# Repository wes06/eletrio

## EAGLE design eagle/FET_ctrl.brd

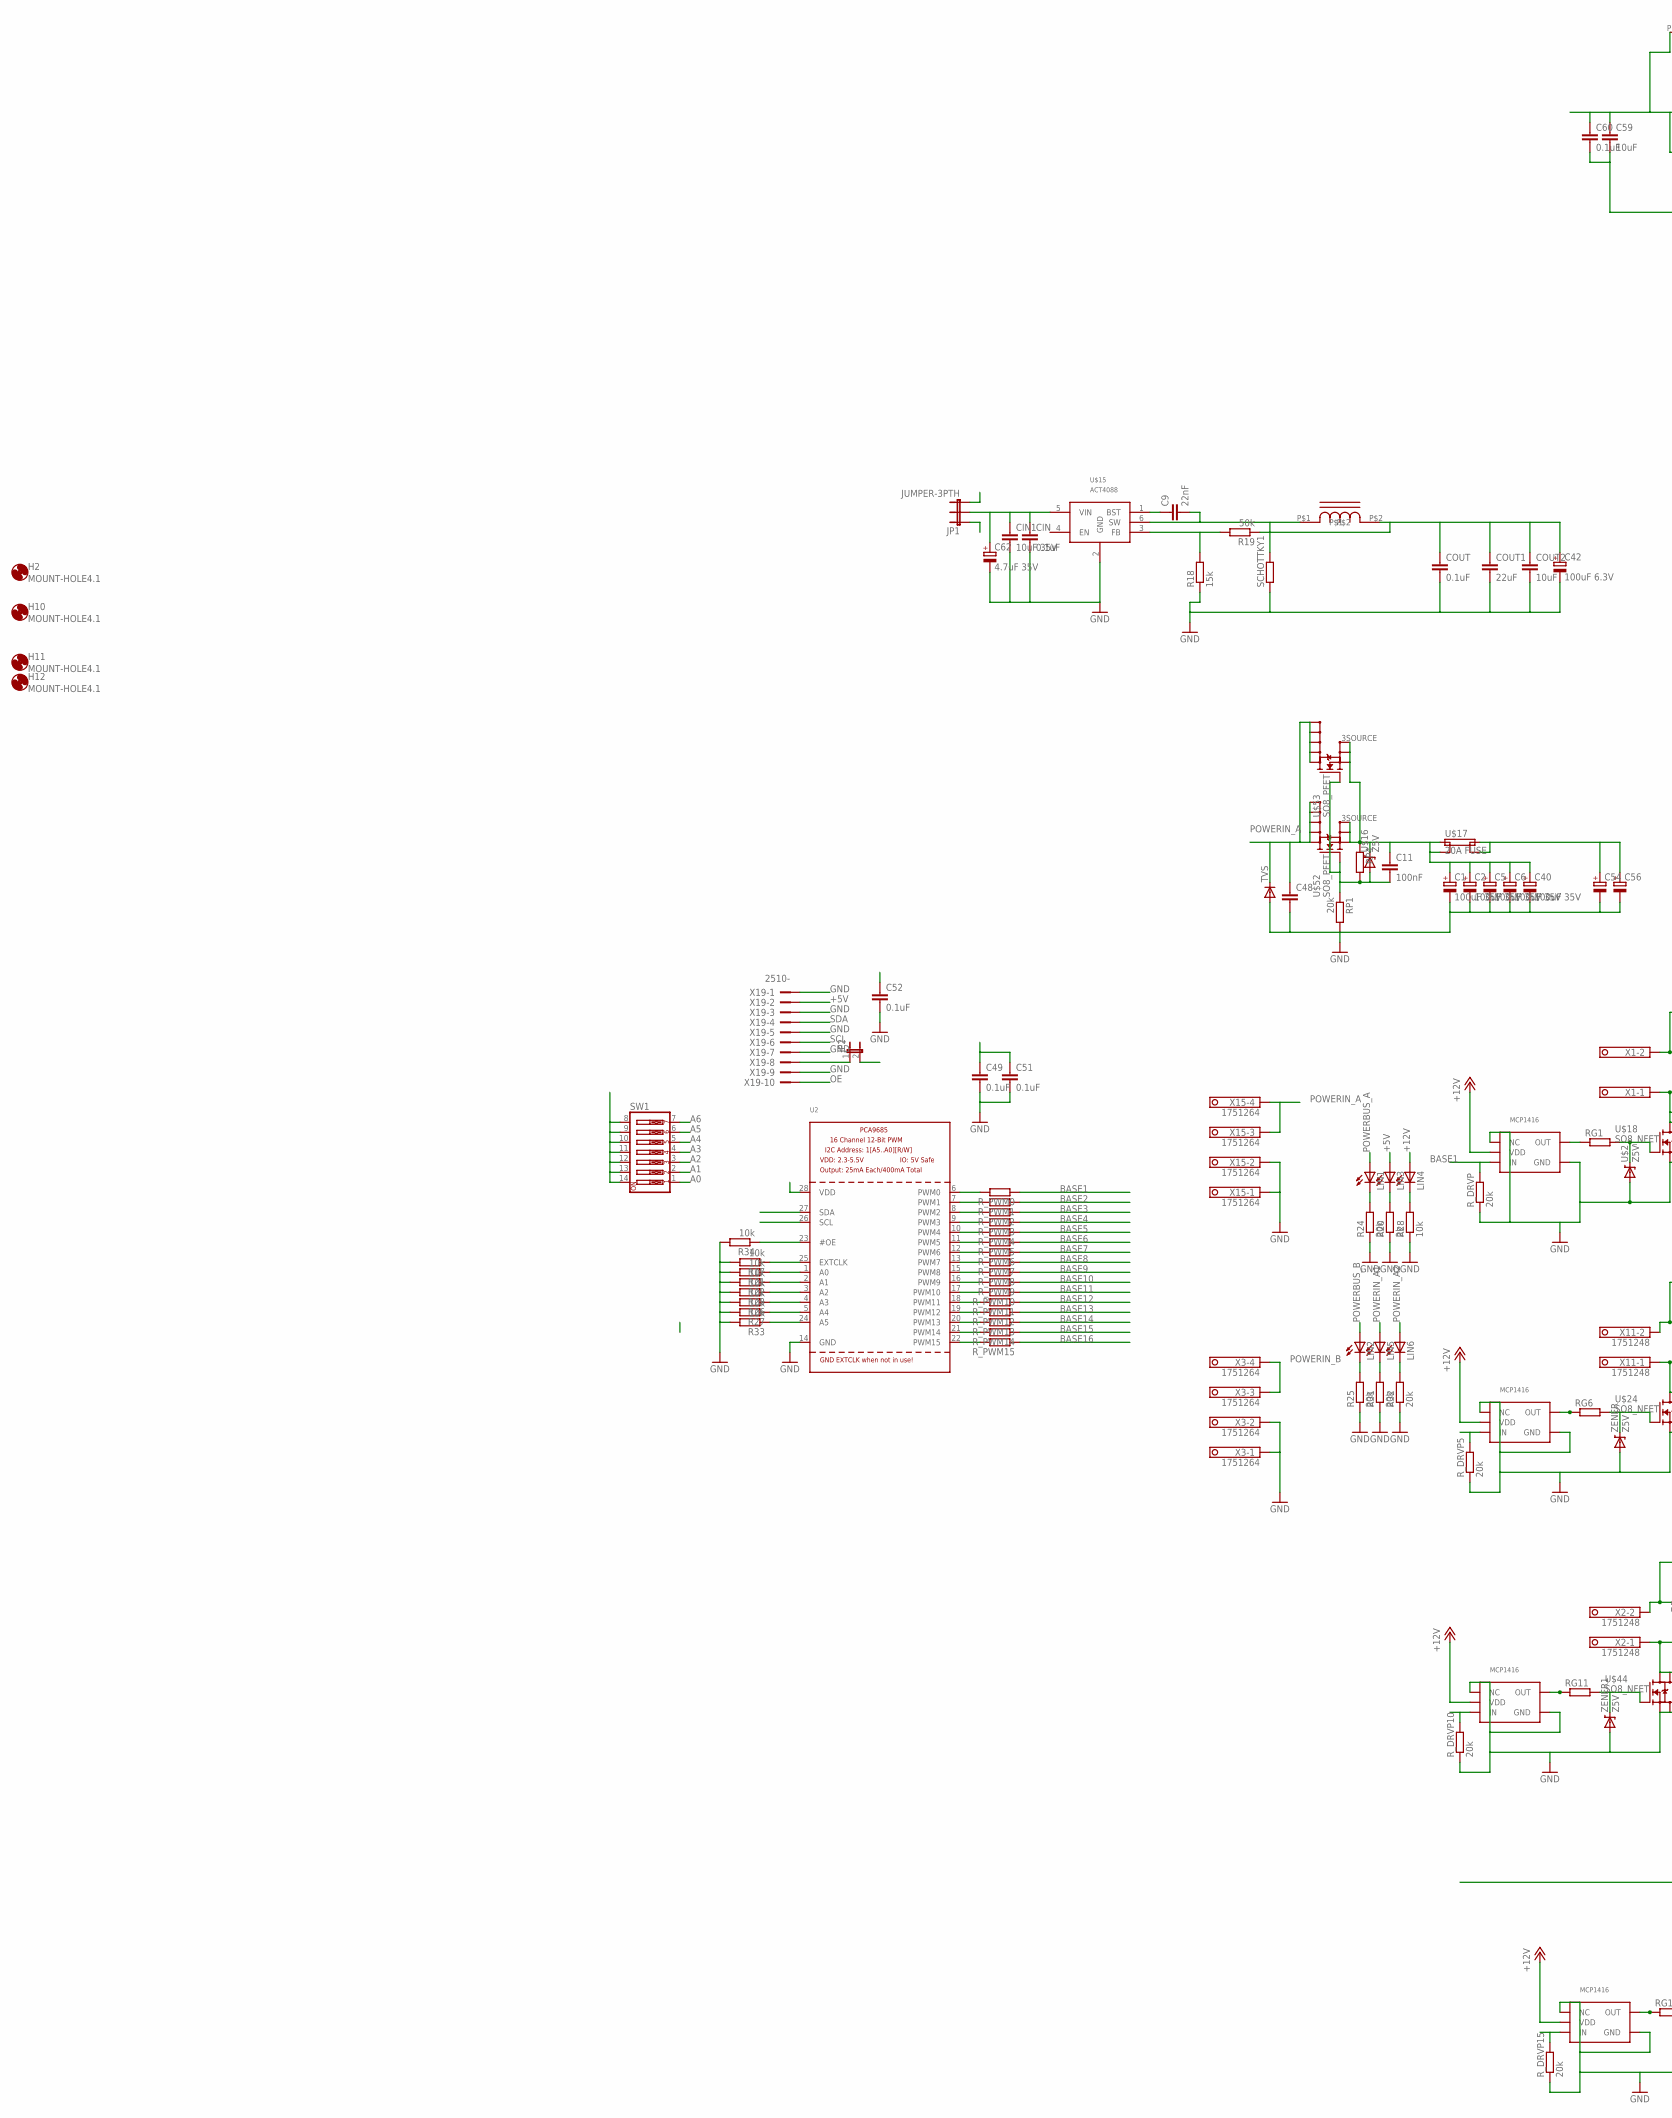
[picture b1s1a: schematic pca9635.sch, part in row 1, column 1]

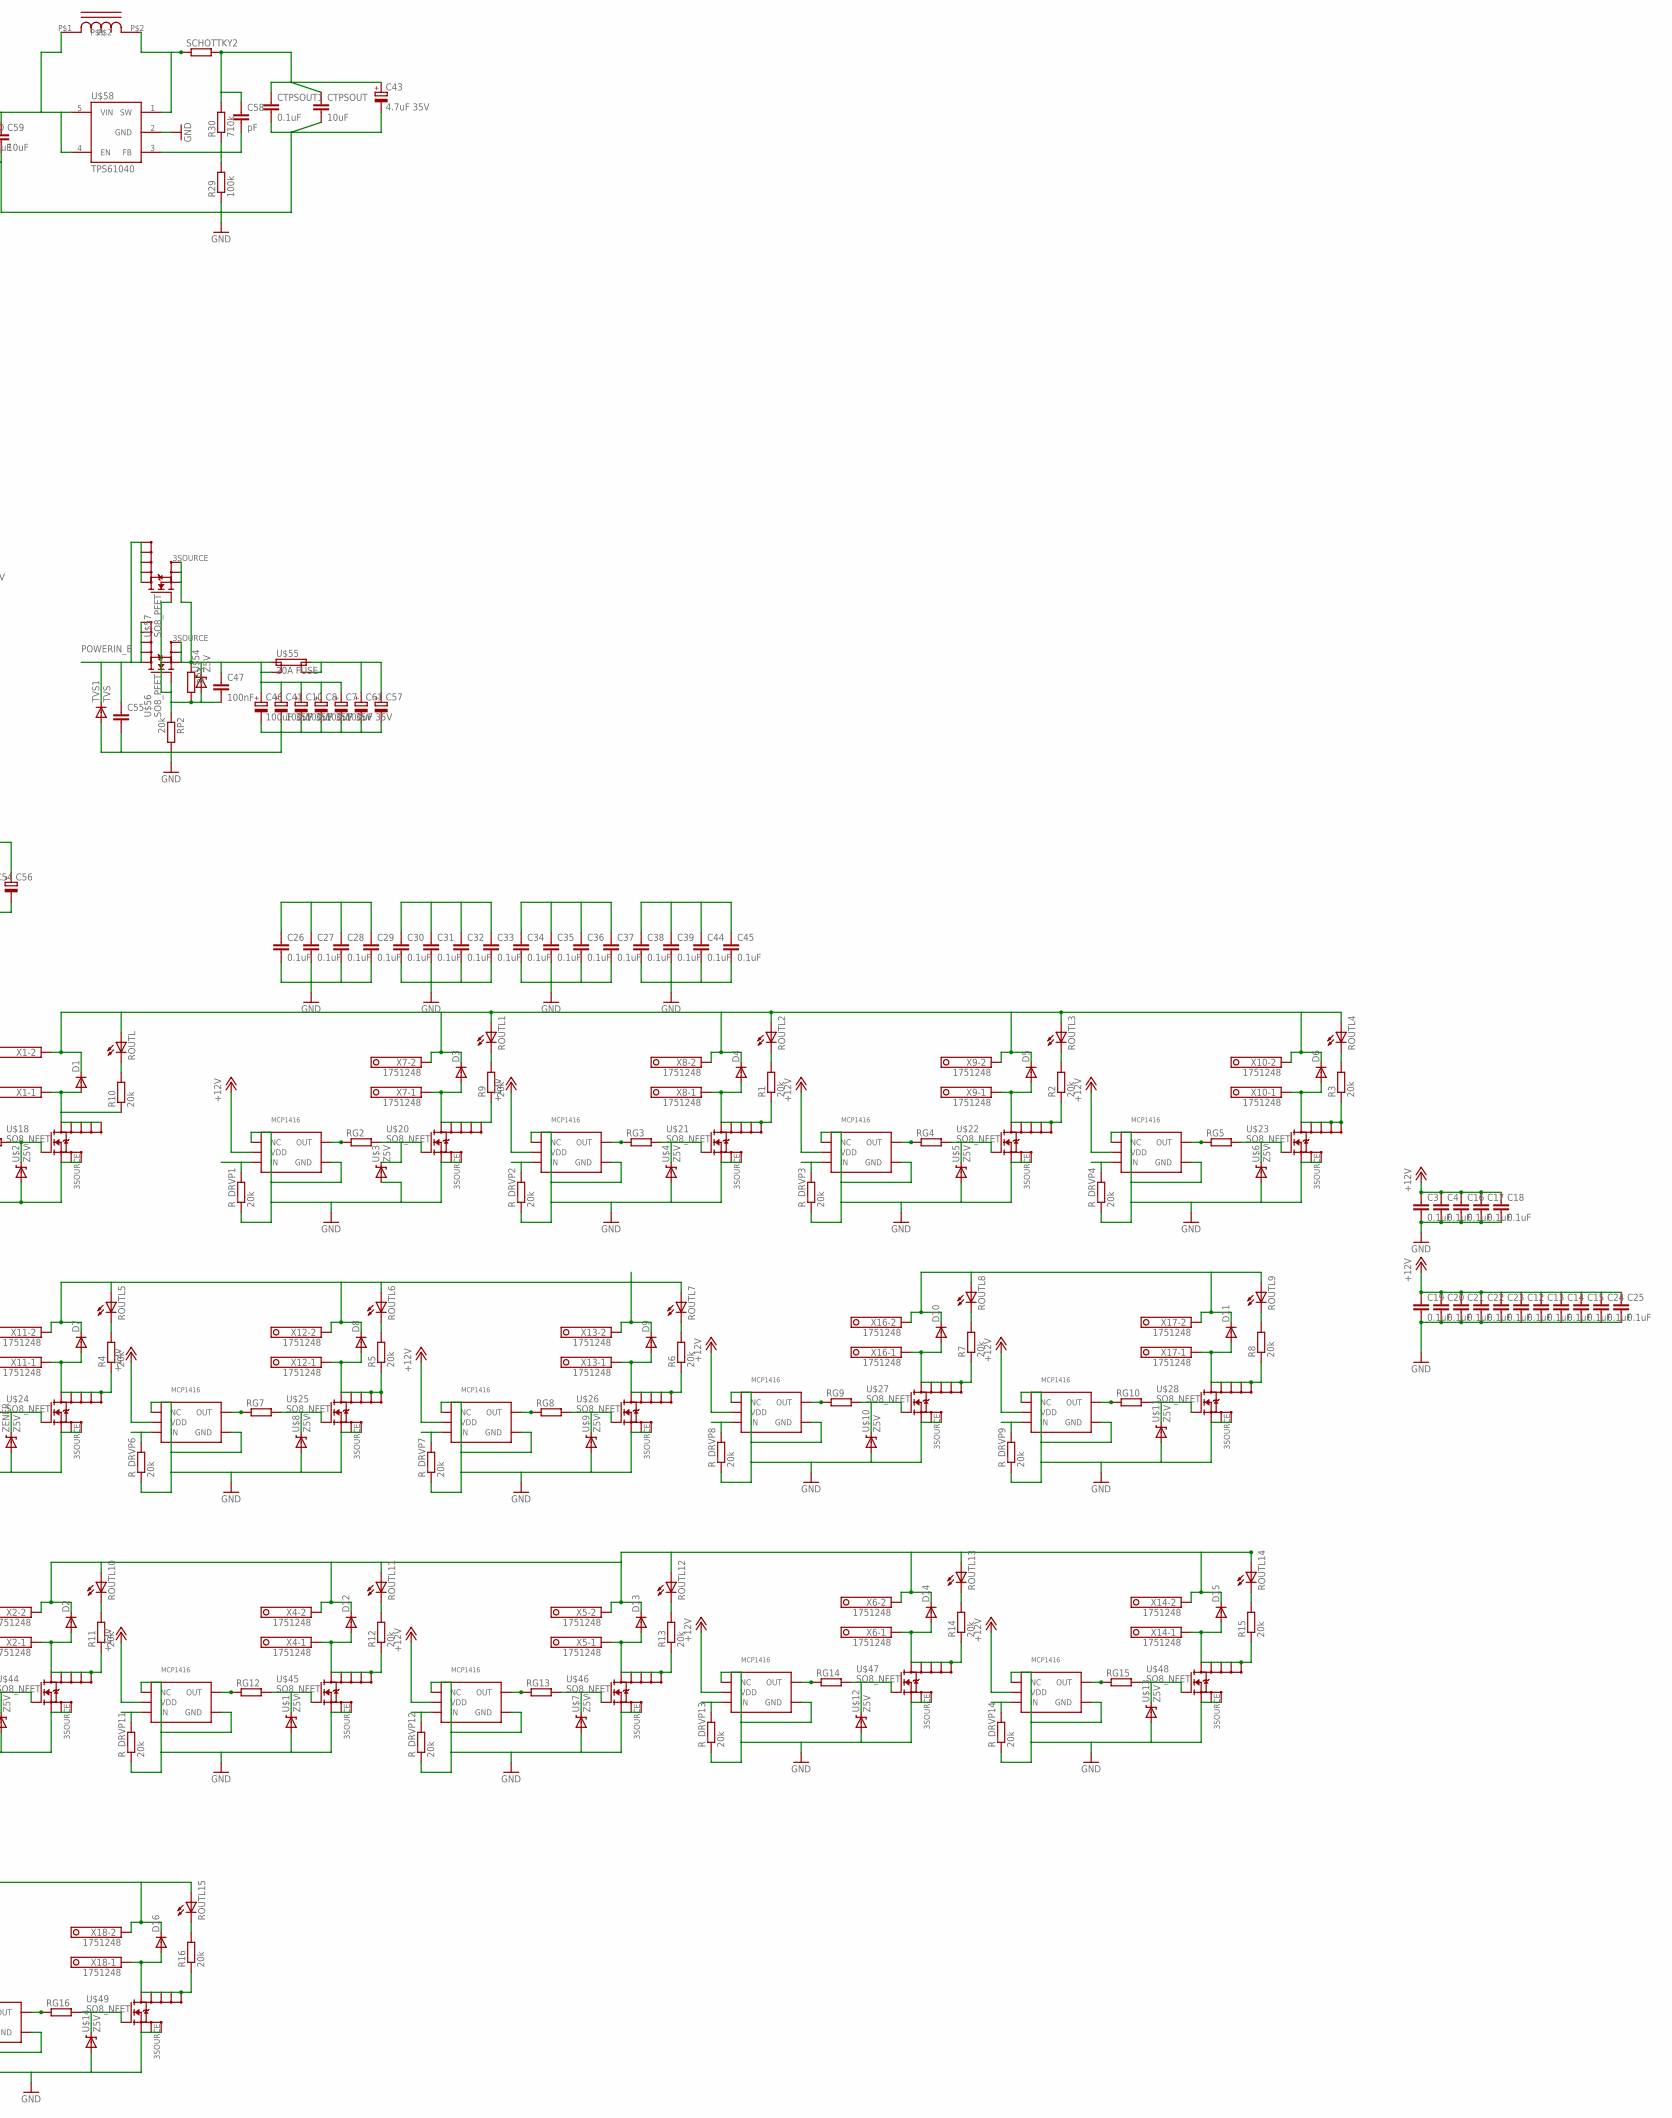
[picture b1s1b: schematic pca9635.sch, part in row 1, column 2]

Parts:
C1, C2, C5, C6, C7, C8, C10, C40, C41, C46: 100uF 35V; SMD_8X10_3.5HOLE
C3, C4, C12, C13, C14, C15, C16, C17, C18, C19, C20, C21, C22, C23, C24, C25, C26, C27, C28, C29, C30, C31, C32, C33, C34, C35, C36, C37, C38, C39, C44, C45, C49, C51, C52, C60: 0.1uF; C0603
C9: 22nF; C0805
C11, C47: 100nF; C0603
C42: 100uF 6.3V; UD-4X5,8_NICHICON
C43, C62: 4.7uF 35V; UD-4X5,8_NICHICON
C48, C55: C-EU050-055X075; C050-055X075
C54, C56, C57, C61: CPOL-EUUD-6,3X7,7; UD-6,3X7,7_NICHICON
C58: pF; C0603
C59: 10uF; C1206
CIN: 0.1uF; C0805
CIN1: 10uF 35V; C1206
COUT: 0.1uF; C0603
COUT1: 22uF; C1210
COUT2: 10uF; C1206
CTPSOUT: 10uF; C1206
CTPSOUT1: 0.1uF; C0805
D1, D2, D3, D4, D5, D6, D7, D8, D9, D10, D11, D12, D13, D14, D15, D16: DIODESMA-ALT; SMA-DIODE_ALT
H2, H10, H11, H12: MOUNT-HOLE4.1; 4,1
JP1: JUMPER-3PTH; 1X03
JP2: JUMPER-2SMD-NO; SJ_2S-NO
LIN1, LIN2, LIN3, LIN4, LIN5, LIN6: LEDCHIP-LED0805; CHIP-LED0805
R1, R2, R3, R4, R5, R6, R7, R8, R9, R10, R11, R12, R13, R14, R15, R16, R24, R25, R31, R32: 20k; R0603
R17, R21, R22, R23, R26, R27, R28, R33, R34: 10k; R0603
R18: 15k; R0603
R19: 50k; R0603
R20: 2k; R0603
R29: 100k; R0603
R30: 710k; R0603
RG1, RG2, RG3, RG4, RG5, RG6, RG7, RG8, RG9, RG10, RG11, RG12, RG13, RG14, RG15, RG16: R-EU_R0603; R0603
ROUTL, ROUTL1, ROUTL2, ROUTL3, ROUTL4, ROUTL5, ROUTL6, ROUTL7, ROUTL8, ROUTL9, ROUTL10, ROUTL11, ROUTL12, ROUTL13, ROUTL14, ROUTL15: LEDCHIP-LED0805; CHIP-LED0805
RP1, RP2: 20k; R0603
RP3, RP4: R-EU_R0603; R0603
R_DRVP, R_DRVP1, R_DRVP2, R_DRVP3, R_DRVP4, R_DRVP5, R_DRVP6, R_DRVP7, R_DRVP8, R_DRVP9, R_DRVP10, R_DRVP11, R_DRVP12, R_DRVP13, R_DRVP14, R_DRVP15: 20k; R0603
R_PWM0, R_PWM1, R_PWM2, R_PWM3, R_PWM4, R_PWM5, R_PWM6, R_PWM7, R_PWM8, R_PWM9, R_PWM10, R_PWM11, R_PWM12, R_PWM13, R_PWM14, R_PWM15: R-EU_R0603; R0603
SCHOTTKY1, SCHOTTKY2: R-EU_R1206; R1206
SW1: SW_DIP-7; EDG-07
TVS: DIODE-SMC; SMC
TVS1: TVS; SMC
U2: PCA9685; TSSOP28
U$1, U$2, U$3, U$4, U$5, U$6, U$7, U$8, U$9, U$10, U$11, U$12, U$13, U$14, U$16, U$54: Z5V; SOD-323
U$15: ACT4088; SOT23-6
U$17, U$55: 20A FUSE; FUSE-3564-297-997
U$18, U$20, U$21, U$22, U$23, U$24, U$25, U$26, U$27, U$28, U$44, U$45, U$46, U$47, U$48, U$49: SO8_NFET; POWER-SO8
U$19, U$29, U$30, U$31, U$32, U$33, U$34, U$35, U$36, U$37, U$38, U$39, U$40, U$41, U$42, U$43: MCP1416; SOT23-5
U$52, U$53, U$56, U$57: SO8_PFET; POWER-SO8
U$58: TPS61040; SOT23-5
U$59, U$60: L1212; 1212
X1, X2, X4, X5, X6, X7, X8, X9, X10, X11, X12, X13, X14, X16, X17, X18: 1751248
X3, X15: 1751264
X19: 2510-; PAK100/2500-10
ZENER, ZENER1: Z5V; SOD-323

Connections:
+5V: C42.+, C49.1, C51.1, C52.1, C59.1, C60.1, COUT.1, COUT1.1, COUT2.1, LIN3.A, R19.1, SW1.8, SW1.9, SW1.10, SW1.11, SW1.12, SW1.13, SW1.14, U2.28 (VDD), U$58.4 (EN), U$58.5 (VIN), U$59.P$1, U$60.P$2, X19.2
+12V: C3.1, C4.1, C12.1, C13.1, C14.1, C15.1, C16.1, C17.1, C18.1, C19.1, C20.1, C21.1, C22.1, C23.1, C24.1, C25.1, C43.+, C58.1, CTPSOUT.1, CTPSOUT1.1, LIN4.A, R30.2, SCHOTTKY2.2, U$19.2 (VDD), U$29.2 (VDD), U$30.2 (VDD), U$31.2 (VDD), U$32.2 (VDD), U$33.2 (VDD), U$34.2 (VDD), U$35.2 (VDD), U$36.2 (VDD), U$37.2 (VDD), U$38.2 (VDD), U$39.2 (VDD), U$40.2 (VDD), U$41.2 (VDD), U$42.2 (VDD), U$43.2 (VDD)
A0: R21.1, SW1.1, U2.1 (A0)
A1: R22.1, SW1.2, U2.2 (A1)
A2: R23.1, SW1.3, U2.3 (A2)
A3: R26.1, SW1.4, U2.4 (A3)
A4: R27.1, SW1.5, U2.5 (A4)
A5: R33.1, SW1.6, U2.24 (A5)
A6: JP2.2, R17.1, SW1.7, U2.25 (EXTCLK)
BASE1: R_DRVP.2, R_PWM0.1, U$19.3 (IN)
BASE2: R_DRVP1.2, R_PWM1.1, U$29.3 (IN)
BASE3: R_DRVP2.2, R_PWM2.1, U$30.3 (IN)
BASE4: R_DRVP3.2, R_PWM3.1, U$31.3 (IN)
BASE5: R_DRVP4.2, R_PWM4.1, U$32.3 (IN)
BASE6: R_DRVP5.2, R_PWM5.1, U$33.3 (IN)
BASE7: R_DRVP6.2, R_PWM6.1, U$34.3 (IN)
BASE8: R_DRVP7.2, R_PWM7.1, U$35.3 (IN)
BASE9: R_DRVP8.2, R_PWM8.1, U$36.3 (IN)
BASE10: R_DRVP9.2, R_PWM9.1, U$37.3 (IN)
BASE11: R_DRVP10.2, R_PWM10.1, U$38.3 (IN)
BASE12: R_DRVP11.2, R_PWM11.1, U$39.3 (IN)
BASE13: R_DRVP12.2, R_PWM12.1, U$40.3 (IN)
BASE14: R_DRVP13.2, R_PWM13.1, U$41.3 (IN)
BASE15: R_DRVP14.2, R_PWM14.1, U$42.3 (IN)
BASE16: R_DRVP15.2, R_PWM15.1, U$43.3 (IN)
EXTCLK: JP2.1, X19.8
GND: C1.-, C1.-1 (-), C2.-, C2.-1 (-), C3.2, C4.2, C5.-, C5.-1 (-), C6.-, C6.-1 (-), C7.-, C7.-1 (-), C8.-, C8.-1 (-), C10.-, C10.-1 (-), C12.2, C13.2, C14.2, C15.2, C16.2, C17.2, C18.2, C19.2, C20.2, C21.2, C22.2, C23.2, C24.2, C25.2, C26.2, C27.2, C28.2, C29.2, C30.2, C31.2, C32.2, C33.2, C34.2, C35.2, C36.2, C37.2, C38.2, C39.2, C40.-, C40.-1 (-), C41.-, C41.-1 (-), C42.-, C43.-, C44.2, C45.2, C46.-, C46.-1 (-), C48.2, C49.2, C51.2, C52.2, C54.-, C55.2, C56.-, C57.-, C59.2, C60.2, C61.-, C62.-, CIN.2, CIN1.2, COUT.2, COUT1.2, COUT2.2, CTPSOUT.2, CTPSOUT1.2, R17.2, R18.1, R20.1, R21.2, R22.2, R23.2, R24.1, R25.1, R26.2, R27.2, R28.1, R29.1, R31.1, R32.1, R33.2, R34.2, RP1.2, RP2.2, R_DRVP.1, R_DRVP1.1, R_DRVP2.1, R_DRVP3.1, R_DRVP4.1, R_DRVP5.1, R_DRVP6.1, R_DRVP7.1, R_DRVP8.1, R_DRVP9.1, R_DRVP10.1, R_DRVP11.1, R_DRVP12.1, R_DRVP13.1, R_DRVP14.1, R_DRVP15.1, SCHOTTKY1.1, TVS.A, TVS1.A, U2.14 (GND), U$1.2 (A), U$2.2 (A), U$3.2 (A), U$4.2 (A), U$5.2 (A), U$6.2 (A), U$7.2 (A), U$8.2 (A), U$9.2 (A), U$10.2 (A), U$11.2 (A), U$12.2 (A), U$13.2 (A), U$14.2 (A), U$15.2 (GND), U$18.1SOURCE (S1), U$18.2SOURCE (S2), U$18.3SOURCE (S3), U$19.1 (NC), U$19.4 (GND), U$20.1SOURCE (S1), U$20.2SOURCE (S2), U$20.3SOURCE (S3), U$21.1SOURCE (S1), U$21.2SOURCE (S2), U$21.3SOURCE (S3), U$22.1SOURCE (S1), U$22.2SOURCE (S2), U$22.3SOURCE (S3), U$23.1SOURCE (S1), U$23.2SOURCE (S2), U$23.3SOURCE (S3), U$24.1SOURCE (S1), U$24.2SOURCE (S2), U$24.3SOURCE (S3), U$25.1SOURCE (S1), U$25.2SOURCE (S2), U$25.3SOURCE (S3), U$26.1SOURCE (S1), U$26.2SOURCE (S2), U$26.3SOURCE (S3), U$27.1SOURCE (S1), U$27.2SOURCE (S2), U$27.3SOURCE (S3), U$28.1SOURCE (S1), U$28.2SOURCE (S2), U$28.3SOURCE (S3), U$29.1 (NC), U$29.4 (GND), U$30.1 (NC), U$30.4 (GND), U$31.1 (NC), U$31.4 (GND), U$32.1 (NC), U$32.4 (GND), U$33.1 (NC), U$33.4 (GND), U$34.1 (NC), U$34.4 (GND), U$35.1 (NC), U$35.4 (GND), U$36.1 (NC), U$36.4 (GND), U$37.1 (NC), U$37.4 (GND), U$38.1 (NC), U$38.4 (GND), U$39.1 (NC), U$39.4 (GND), U$40.1 (NC), U$40.4 (GND), U$41.1 (NC), U$41.4 (GND), U$42.1 (NC), U$42.4 (GND), U$43.1 (NC), U$43.4 (GND), U$44.1SOURCE (S1), U$44.2SOURCE (S2), U$44.3SOURCE (S3), U$45.1SOURCE (S1), U$45.2SOURCE (S2), U$45.3SOURCE (S3), U$46.1SOURCE (S1), U$46.2SOURCE (S2), U$46.3SOURCE (S3), U$47.1SOURCE (S1), U$47.2SOURCE (S2), U$47.3SOURCE (S3), U$48.1SOURCE (S1), U$48.2SOURCE (S2), U$48.3SOURCE (S3), U$49.1SOURCE (S1), U$49.2SOURCE (S2), U$49.3SOURCE (S3), U$58.2 (GND), X3.1, X3.2, X15.1, X15.2, X19.1, X19.3, X19.5, X19.7, X19.9, ZENER.2 (A), ZENER1.2 (A)
unnamed: D1.A, R10.1, U$18.5DRAIN (D5), U$18.6DRAIN (D6), U$18.7DRAIN (D7), U$18.8DRAIN (D8), U$18.PAD_DRAIN (DPAD), X1.1
unnamed: R10.2, ROUTL.C
unnamed: D2.A, R11.1, U$44.5DRAIN (D5), U$44.6DRAIN (D6), U$44.7DRAIN (D7), U$44.8DRAIN (D8), U$44.PAD_DRAIN (DPAD), X2.1
unnamed: RG11.2, U$44.4GATE (G), ZENER1.1 (C)
unnamed: LIN3.C, R20.2
unnamed: D12.A, R12.1, U$45.5DRAIN (D5), U$45.6DRAIN (D6), U$45.7DRAIN (D7), U$45.8DRAIN (D8), U$45.PAD_DRAIN (DPAD), X4.1
unnamed: RG12.2, U$1.1 (C), U$45.4GATE (G)
unnamed: R1.2, ROUTL2.C
unnamed: D13.A, R13.1, U$46.5DRAIN (D5), U$46.6DRAIN (D6), U$46.7DRAIN (D7), U$46.8DRAIN (D8), U$46.PAD_DRAIN (DPAD), X5.1
unnamed: RG13.2, U$7.1 (C), U$46.4GATE (G)
unnamed: C47.2, RP2.1, RP3.2, U$54.2 (A), U$56.4GATE (G), U$57.4GATE (G)
unnamed: D14.A, R14.1, U$47.5DRAIN (D5), U$47.6DRAIN (D6), U$47.7DRAIN (D7), U$47.8DRAIN (D8), U$47.PAD_DRAIN (DPAD), X6.1
unnamed: RG14.2, U$12.1 (C), U$47.4GATE (G)
unnamed: R2.2, ROUTL3.C
unnamed: LIN2.C, R25.2
unnamed: D15.A, R15.1, U$48.5DRAIN (D5), U$48.6DRAIN (D6), U$48.7DRAIN (D7), U$48.8DRAIN (D8), U$48.PAD_DRAIN (DPAD), X14.1
unnamed: RG15.2, U$13.1 (C), U$48.4GATE (G)
unnamed: LIN4.C, R28.2
unnamed: R_PWM0.2, U2.6 (PWM0)
unnamed: R_PWM1.2, U2.7 (PWM1)
unnamed: R_PWM15.2, U2.22 (PWM15)
unnamed: R_PWM14.2, U2.21 (PWM14)
unnamed: R_PWM13.2, U2.20 (PWM13)
unnamed: D16.A, R16.1, U$49.5DRAIN (D5), U$49.6DRAIN (D6), U$49.7DRAIN (D7), U$49.8DRAIN (D8), U$49.PAD_DRAIN (DPAD), X18.1
unnamed: RG16.2, U$14.1 (C), U$49.4GATE (G)
unnamed: R3.2, ROUTL4.C
unnamed: R_PWM12.2, U2.19 (PWM12)
unnamed: R18.2, R19.2, U$15.3 (FB)
unnamed: C9.1, U$15.1 (BST)
unnamed: SCHOTTKY2.1, U$58.1 (SW), U$59.P$2
unnamed: LIN5.C, R31.2
unnamed: C58.2, R29.2, R30.1, U$58.3 (FB)
unnamed: LIN1.C, R24.2
unnamed: LIN6.C, R32.2
unnamed: C11.2, RP1.1, RP4.2, U$16.2 (A), U$52.4GATE (G), U$53.4GATE (G)
unnamed: RG1.1, U$19.5 (OUT)
unnamed: R_PWM11.2, U2.18 (PWM11)
unnamed: R_PWM10.2, U2.17 (PWM10)
unnamed: R_PWM9.2, U2.16 (PWM9)
unnamed: R_PWM8.2, U2.15 (PWM8)
unnamed: R_PWM7.2, U2.13 (PWM7)
unnamed: R_PWM6.2, U2.12 (PWM6)
unnamed: R_PWM5.2, U2.11 (PWM5)
unnamed: R_PWM4.2, U2.10 (PWM4)
unnamed: R_PWM3.2, U2.9 (PWM3)
unnamed: R_PWM2.2, U2.8 (PWM2)
unnamed: RG2.1, U$29.5 (OUT)
unnamed: RG3.1, U$30.5 (OUT)
unnamed: RG4.1, U$31.5 (OUT)
unnamed: D3.A, R9.1, U$20.5DRAIN (D5), U$20.6DRAIN (D6), U$20.7DRAIN (D7), U$20.8DRAIN (D8), U$20.PAD_DRAIN (DPAD), X7.1
unnamed: RG2.2, U$3.1 (C), U$20.4GATE (G)
unnamed: RG5.1, U$32.5 (OUT)
unnamed: RG6.1, U$33.5 (OUT)
unnamed: D4.A, R1.1, U$21.5DRAIN (D5), U$21.6DRAIN (D6), U$21.7DRAIN (D7), U$21.8DRAIN (D8), U$21.PAD_DRAIN (DPAD), X8.1
unnamed: RG7.1, U$34.5 (OUT)
unnamed: RG8.1, U$35.5 (OUT)
unnamed: RG3.2, U$4.1 (C), U$21.4GATE (G)
unnamed: R4.2, ROUTL5.C
unnamed: RG9.1, U$36.5 (OUT)
unnamed: RG10.1, U$37.5 (OUT)
unnamed: RG1.2, U$2.1 (C), U$18.4GATE (G)
unnamed: RG4.2, U$5.1 (C), U$22.4GATE (G)
unnamed: RG11.1, U$38.5 (OUT)
unnamed: RG12.1, U$39.5 (OUT)
unnamed: D6.A, R3.1, U$23.5DRAIN (D5), U$23.6DRAIN (D6), U$23.7DRAIN (D7), U$23.8DRAIN (D8), U$23.PAD_DRAIN (DPAD), X10.1
unnamed: RG13.1, U$40.5 (OUT)
unnamed: RG14.1, U$41.5 (OUT)
unnamed: RG5.2, U$6.1 (C), U$23.4GATE (G)
unnamed: R5.2, ROUTL6.C
unnamed: RG15.1, U$42.5 (OUT)
unnamed: RG16.1, U$43.5 (OUT)
unnamed: R9.2, ROUTL1.C
unnamed: R6.2, ROUTL7.C
unnamed: R7.2, ROUTL8.C
unnamed: R8.2, ROUTL9.C
unnamed: R11.2, ROUTL10.C
unnamed: R12.2, ROUTL11.C
unnamed: R13.2, ROUTL12.C
unnamed: R14.2, ROUTL13.C
unnamed: R15.2, ROUTL14.C
unnamed: D10.A, R7.1, U$27.5DRAIN (D5), U$27.6DRAIN (D6), U$27.7DRAIN (D7), U$27.8DRAIN (D8), U$27.PAD_DRAIN (DPAD), X16.1
unnamed: R16.2, ROUTL15.C
unnamed: RG9.2, U$10.1 (C), U$27.4GATE (G)
unnamed: D11.A, R8.1, U$28.5DRAIN (D5), U$28.6DRAIN (D6), U$28.7DRAIN (D7), U$28.8DRAIN (D8), U$28.PAD_DRAIN (DPAD), X17.1
unnamed: RG10.2, U$11.1 (C), U$28.4GATE (G)
unnamed: D7.A, R4.1, U$24.5DRAIN (D5), U$24.6DRAIN (D6), U$24.7DRAIN (D7), U$24.8DRAIN (D8), U$24.PAD_DRAIN (DPAD), X11.1
unnamed: RG6.2, U$24.4GATE (G), ZENER.1 (C)
unnamed: D8.A, R5.1, U$25.5DRAIN (D5), U$25.6DRAIN (D6), U$25.7DRAIN (D7), U$25.8DRAIN (D8), U$25.PAD_DRAIN (DPAD), X12.1
unnamed: RG7.2, U$8.1 (C), U$25.4GATE (G)
unnamed: D9.A, R6.1, U$26.5DRAIN (D5), U$26.6DRAIN (D6), U$26.7DRAIN (D7), U$26.8DRAIN (D8), U$26.PAD_DRAIN (DPAD), X13.1
unnamed: RG8.2, U$9.1 (C), U$26.4GATE (G)
OE: R34.1, U2.23 (#OE), X19.10
POWERBUS_A: C26.1, C27.1, C28.1, C29.1, C30.1, C31.1, C32.1, C33.1, C54.+, C56.+, D1.C, D3.C, D4.C, D5.C, D6.C, D7.C, D8.C, D9.C, JP1.3, LIN1.A, ROUTL.A, ROUTL1.A, ROUTL2.A, ROUTL3.A, ROUTL4.A, ROUTL5.A, ROUTL6.A, ROUTL7.A, U$17.P$3 (2A), U$17.P$4 (2B), X1.2, X7.2, X8.2, X9.2, X10.2, X11.2, X12.2, X13.2
POWERBUS_B: C34.1, C35.1, C36.1, C37.1, C38.1, C39.1, C44.1, C45.1, C57.+, C61.+, D2.C, D10.C, D11.C, D12.C, D13.C, D14.C, D15.C, D16.C, JP1.1, LIN2.A, ROUTL8.A, ROUTL9.A, ROUTL10.A, ROUTL11.A, ROUTL12.A, ROUTL13.A, ROUTL14.A, ROUTL15.A, U$55.P$3 (2A), U$55.P$4 (2B), X2.2, X4.2, X5.2, X6.2, X14.2, X16.2, X17.2, X18.2
POWERIN_A: C48.1, TVS.C, U$52.5DRAIN (D5), U$52.6DRAIN (D6), U$52.7DRAIN (D7), U$52.8DRAIN (D8), U$52.PAD_DRAIN (DPAD), U$53.5DRAIN (D5), U$53.6DRAIN (D6), U$53.7DRAIN (D7), U$53.8DRAIN (D8), U$53.PAD_DRAIN (DPAD), X15.3, X15.4
POWERIN_A1: C1.+, C1.+2 (+), C2.+, C2.+2 (+), C5.+, C5.+2 (+), C6.+, C6.+2 (+), C11.1, C40.+, C40.+2 (+), LIN5.A, RP4.1, U$16.1 (C), U$17.P$1 (1A), U$17.P$2 (1B), U$52.1SOURCE (S1), U$52.2SOURCE (S2), U$52.3SOURCE (S3), U$53.1SOURCE (S1), U$53.2SOURCE (S2), U$53.3SOURCE (S3)
POWERIN_A2: C7.+, C7.+2 (+), C8.+, C8.+2 (+), C10.+, C10.+2 (+), C41.+, C41.+2 (+), C46.+, C46.+2 (+), C47.1, LIN6.A, RP3.1, U$54.1 (C), U$55.P$1 (1A), U$55.P$2 (1B), U$56.1SOURCE (S1), U$56.2SOURCE (S2), U$56.3SOURCE (S3), U$57.1SOURCE (S1), U$57.2SOURCE (S2), U$57.3SOURCE (S3)
POWERIN_B: C55.1, TVS1.C, U$56.5DRAIN (D5), U$56.6DRAIN (D6), U$56.7DRAIN (D7), U$56.8DRAIN (D8), U$56.PAD_DRAIN (DPAD), U$57.5DRAIN (D5), U$57.6DRAIN (D6), U$57.7DRAIN (D7), U$57.8DRAIN (D8), U$57.PAD_DRAIN (DPAD), X3.3, X3.4
Q4: D5.A, R2.1, U$22.5DRAIN (D5), U$22.6DRAIN (D6), U$22.7DRAIN (D7), U$22.8DRAIN (D8), U$22.PAD_DRAIN (DPAD), X9.1
SCL: U2.26 (SCL), X19.6
SDA: U2.27 (SDA), X19.4
SW: C9.2, SCHOTTKY1.2, U$15.6 (SW), U$60.P$1
VIN: C62.+, CIN.1, CIN1.1, JP1.2, U$15.5 (VIN)

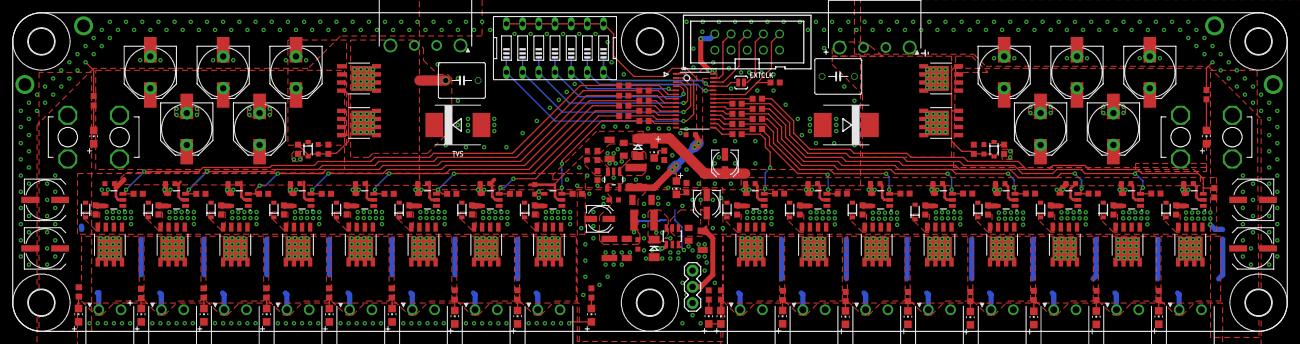
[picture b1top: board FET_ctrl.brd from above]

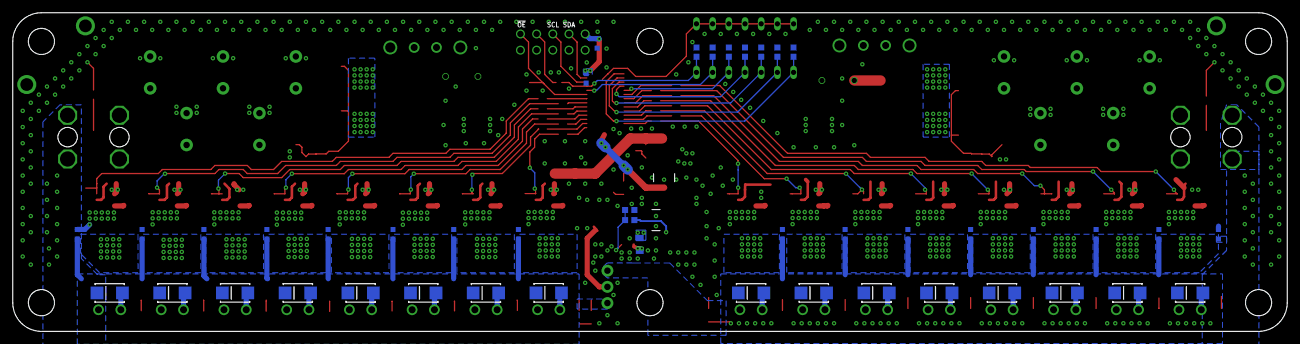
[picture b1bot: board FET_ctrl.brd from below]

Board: 2 copper layers, 200.0 x 50.0 mm, 284 parts (44 on the bottom side), 130 nets.

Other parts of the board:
H1, H9: MOUNT-HOLE4.1; 4,1

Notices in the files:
parts and their libraries:
SparkFun-DiscreteSemi: Licensing: CC v3.0 Share-Alike You are welcome to use this library for commercial purposes.
